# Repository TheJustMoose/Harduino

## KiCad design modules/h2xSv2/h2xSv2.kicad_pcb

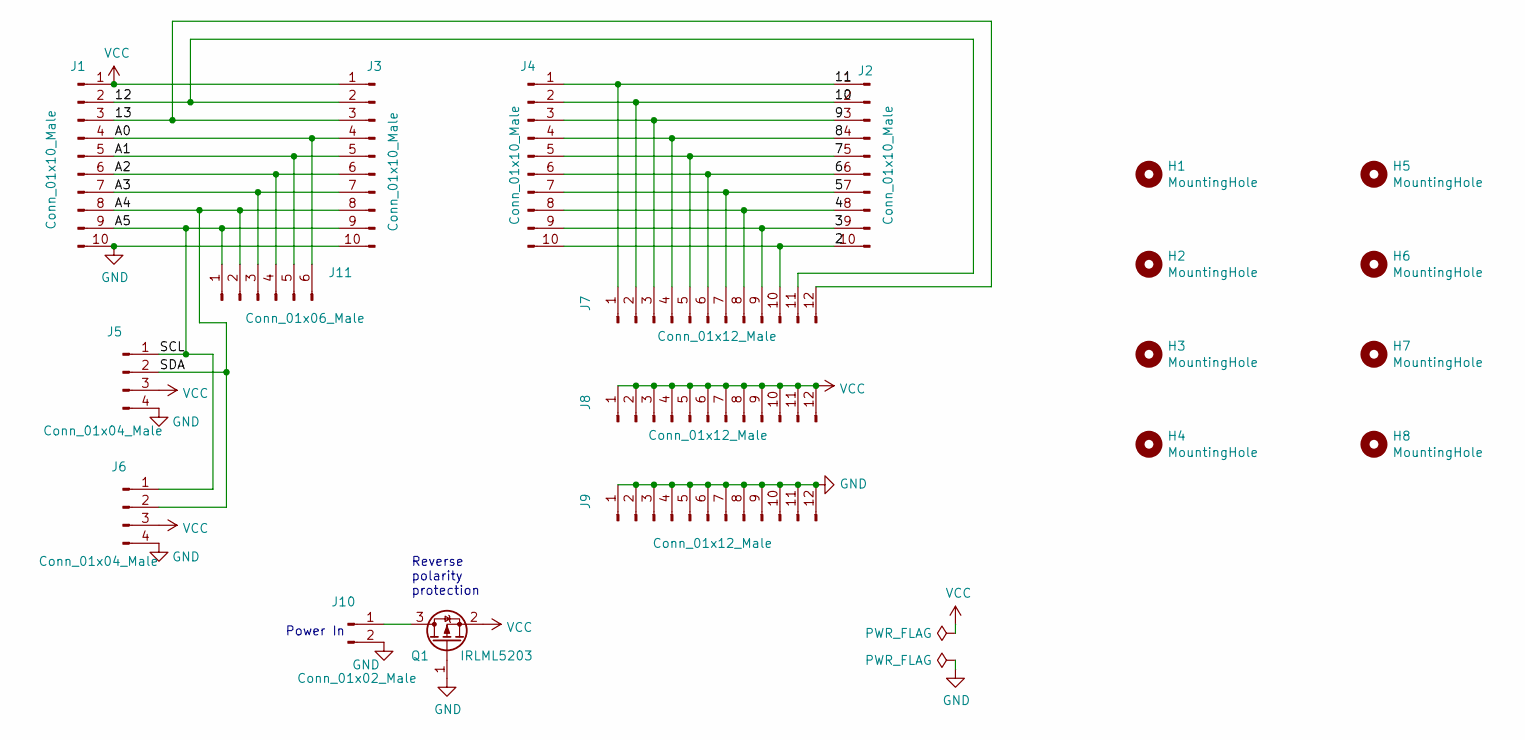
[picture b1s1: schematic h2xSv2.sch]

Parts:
H1, H2, H3, H4, H5, H6, H7, H8: MountingHole; MountingHole_3.2mm_M3
J1, J2, J3, J4: Conn_01x10_Male; PinSocket_1x10_P2.54mm_Vertical
J5, J6: Conn_01x04_Male; PinHeader_1x04_P2.54mm_Vertical
J7, J8, J9: Conn_01x12_Male; PinHeader_1x12_P2.54mm_Vertical
J10: Conn_01x02_Male; PinHeader_1x02_P2.54mm_Vertical
J11: Conn_01x06_Male; PinHeader_1x06_P2.54mm_Vertical
Q1: IRLML5203; SOT-23

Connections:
/2: J2.10, J4.10, J7.10
/3: J2.9, J4.9, J7.9
/4: J2.8, J4.8, J7.8
/5: J2.7, J4.7, J7.7
/6: J2.6, J4.6, J7.6
/7: J2.5, J4.5, J7.5
/8: J2.4, J4.4, J7.4
/9: J2.3, J4.3, J7.3
/10: J2.2, J4.2, J7.2
/11: J2.1, J4.1, J7.1
/12: J1.2, J3.2, J7.11
/13: J1.3, J3.3, J7.12
/A0: J1.4, J3.4, J11.6
/A1: J1.5, J3.5, J11.5
/A2: J1.6, J3.6, J11.4
/A3: J1.7, J3.7, J11.3
/A4: J1.8, J3.8, J5.2, J6.2, J11.2
/A5: J1.9, J3.9, J5.1, J6.1, J11.1
GND: J1.10, J3.10, J5.4, J6.4, J9.1, J9.2, J9.3, J9.4, J9.5, J9.6, J9.7, J9.8, J9.9, J9.10, J9.11, J9.12, J10.2, Q1.1 (G)
unnamed: J10.1, Q1.3 (D)
VCC: J1.1, J3.1, J5.3, J6.3, J8.1, J8.2, J8.3, J8.4, J8.5, J8.6, J8.7, J8.8, J8.9, J8.10, J8.11, J8.12, Q1.2 (S)

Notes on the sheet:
Power In
Reverse polarity protection

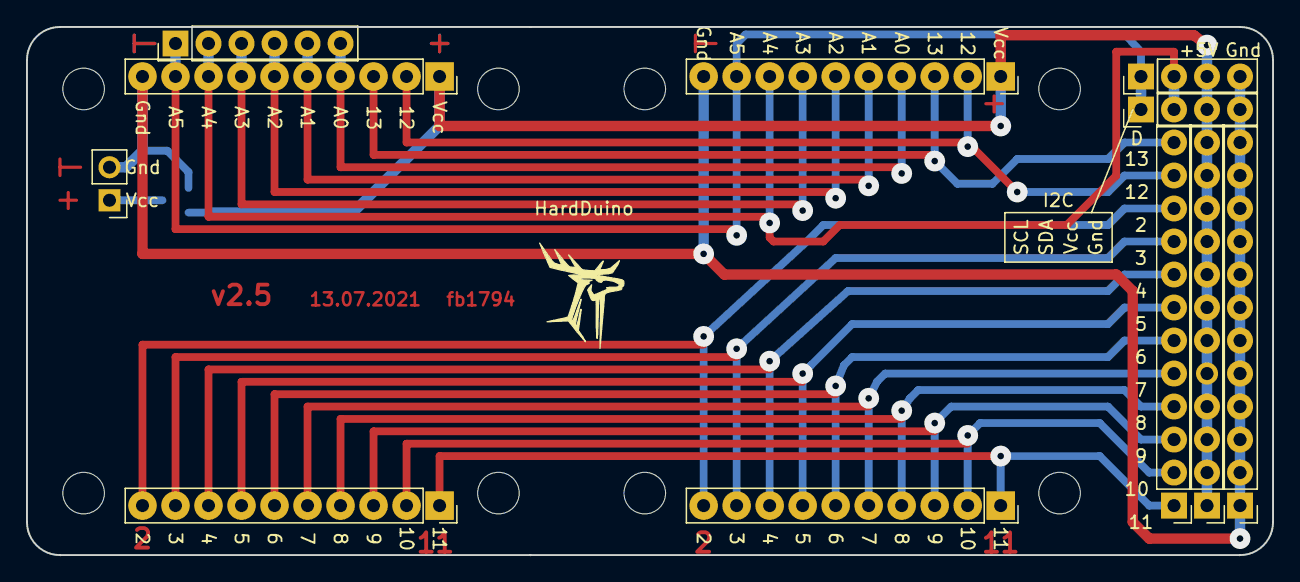
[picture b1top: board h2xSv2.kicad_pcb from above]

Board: 2 copper layers, 95.9 x 40.6 mm, 20 parts (1 on the bottom side), 21 nets.

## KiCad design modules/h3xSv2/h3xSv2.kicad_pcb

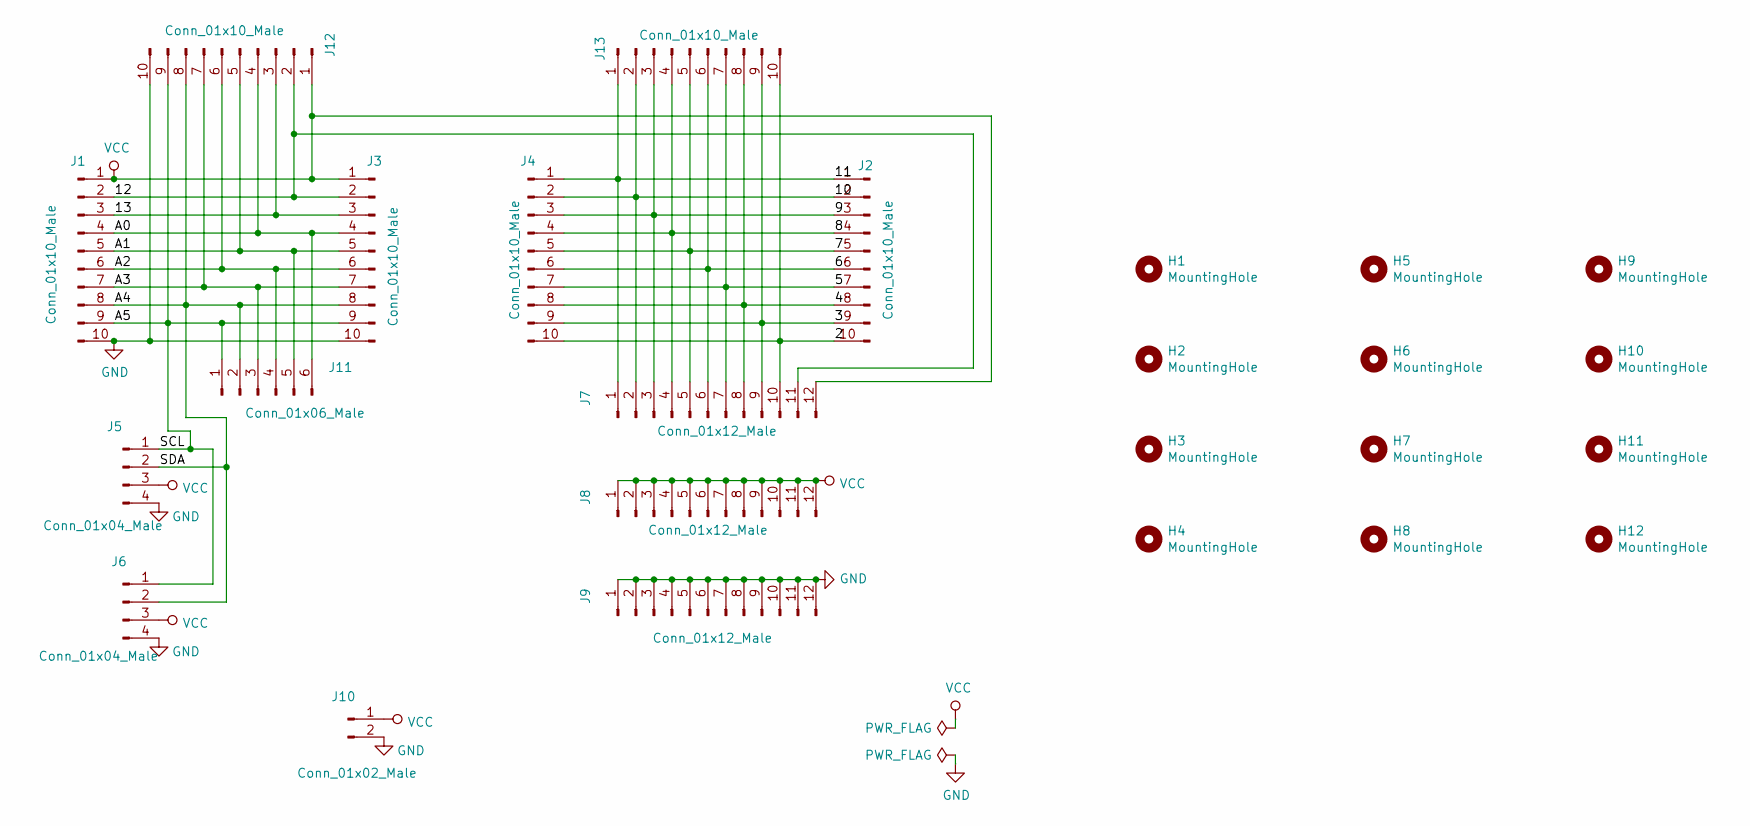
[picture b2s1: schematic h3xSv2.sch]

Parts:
H1, H2, H3, H4, H5, H6, H7, H8, H9, H10, H11, H12: MountingHole; MountingHole_3.2mm_M3
J1, J2, J3, J4, J12, J13: Conn_01x10_Male; PinSocket_1x10_P2.54mm_Vertical
J5, J6: Conn_01x04_Male; PinHeader_1x04_P2.54mm_Vertical
J7, J8, J9: Conn_01x12_Male; PinHeader_1x12_P2.54mm_Vertical
J10: Conn_01x02_Male; PinHeader_1x02_P2.54mm_Vertical
J11: Conn_01x06_Male; PinHeader_1x06_P2.54mm_Vertical

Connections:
/2: J2.10, J4.10, J7.10, J13.10
/3: J2.9, J4.9, J7.9, J13.9
/4: J2.8, J4.8, J7.8, J13.8
/5: J2.7, J4.7, J7.7, J13.7
/6: J2.6, J4.6, J7.6, J13.6
/7: J2.5, J4.5, J7.5, J13.5
/8: J2.4, J4.4, J7.4, J13.4
/9: J2.3, J4.3, J7.3, J13.3
/10: J2.2, J4.2, J7.2, J13.2
/11: J2.1, J4.1, J7.1, J13.1
/12: J1.2, J3.2, J7.11, J12.2
/A0: J1.4, J3.4, J11.6, J12.4
/A1: J1.5, J3.5, J11.5, J12.5
/A2: J1.6, J3.6, J11.4, J12.6
/A3: J1.7, J3.7, J11.3, J12.7
/A4: J1.8, J3.8, J5.2, J6.2, J11.2, J12.8
/A5: J1.9, J3.9, J5.1, J6.1, J11.1, J12.9
GND: J1.10, J3.10, J5.4, J6.4, J9.1, J9.2, J9.3, J9.4, J9.5, J9.6, J9.7, J9.8, J9.9, J9.10, J9.11, J9.12, J10.2, J12.10

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
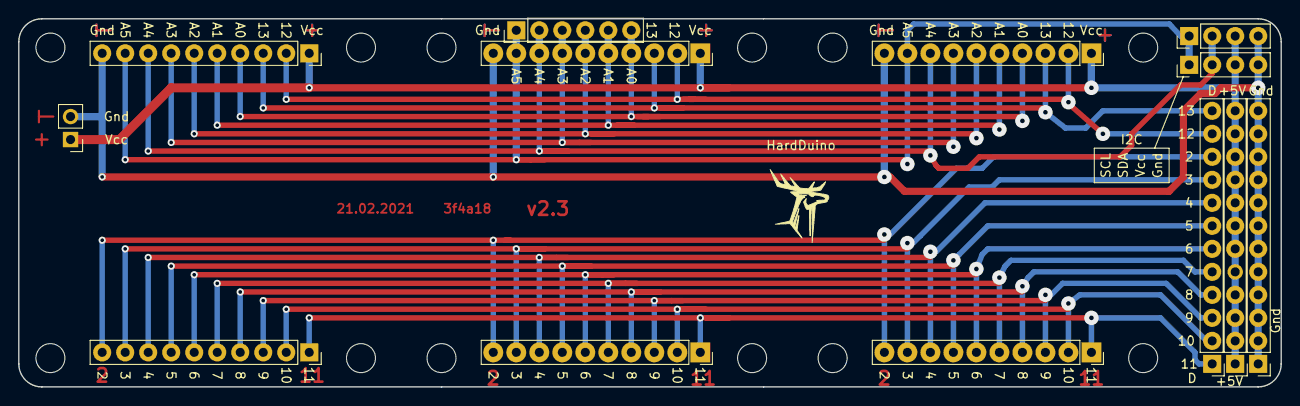
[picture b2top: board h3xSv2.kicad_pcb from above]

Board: 2 copper layers, 139.4 x 40.6 mm, 25 parts (0 on the bottom side), 20 nets.
